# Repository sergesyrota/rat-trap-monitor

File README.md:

Power consumption with deep sleep mode (ping every 5 min): ~70mW?

Power consumption without deep sleep: ~700mW?

Calibration values for voltage conversion
```
1066 -> 10.5V
1142 -> 11.3V
1211 -> 11.9V
1274 -> 12.6V
1407 -> 13.9V
```

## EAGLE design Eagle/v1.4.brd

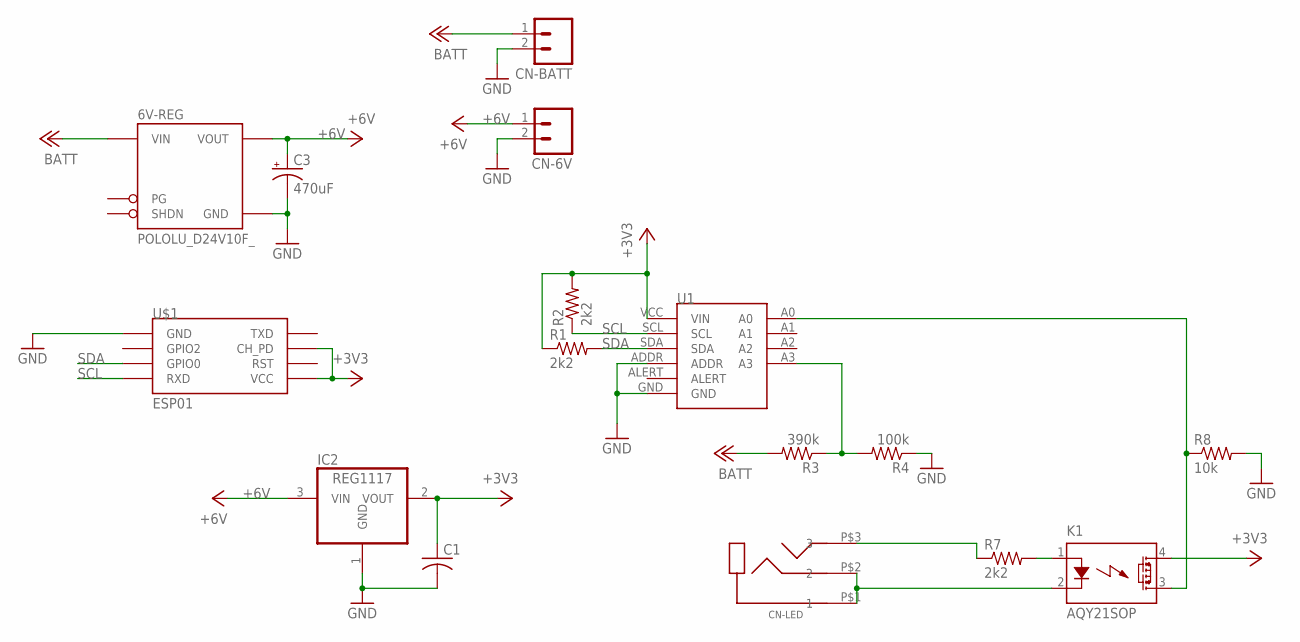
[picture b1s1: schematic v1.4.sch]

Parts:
6V-REG: POLOLU_D24V10F_; POLOLU_D24V10
C1: C-USC1210; C1210
C3: 470uF; CPOL-RADIAL-2.5MM-6.5MM
CN-6V: M02; 02P
CN-BATT: M02; 02P
CN-LED: PJ-320B
IC2: REG1117; SOT223
K1: AQY21SOP; SOP04
R1, R2, R7: 2k2; R0603
R3: 390k; R0603
R4: 100k; R0603
R8: 10k; R0603
U1: GY-ADS1115THM; GY-ADS1115-THM
U$1: ESP01

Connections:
+3V3: C1.1, IC2.2 (VOUT), K1.4 (DS1), R1.1, R2.2, U1.VCC (VIN), U$1.CH_PD, U$1.VCC
+6V: 6V-REG.VOUT, C3.1 (+), CN-6V.1, IC2.3 (VIN)
+12V: 6V-REG.VIN, CN-BATT.1, R3.2
GND: 6V-REG.GND, C1.2, C3.2 (-), CN-6V.2, CN-BATT.2, IC2.1 (GND), R4.1, R8.2, U1.ADDR, U1.GND, U$1.GND
unnamed: K1.1 (A), R7.2
unnamed: R3.1, R4.2, U1.A3
unnamed: CN-LED.P$3 (3), R7.1
unnamed: K1.3 (DS2), R8.1, U1.A0
unnamed: CN-LED.P$1 (1), CN-LED.P$2 (2), K1.2 (K)
SCL: R2.1, U1.SCL, U$1.RX (RXD)
SDA: R1.2, U1.SDA, U$1.GPIO0

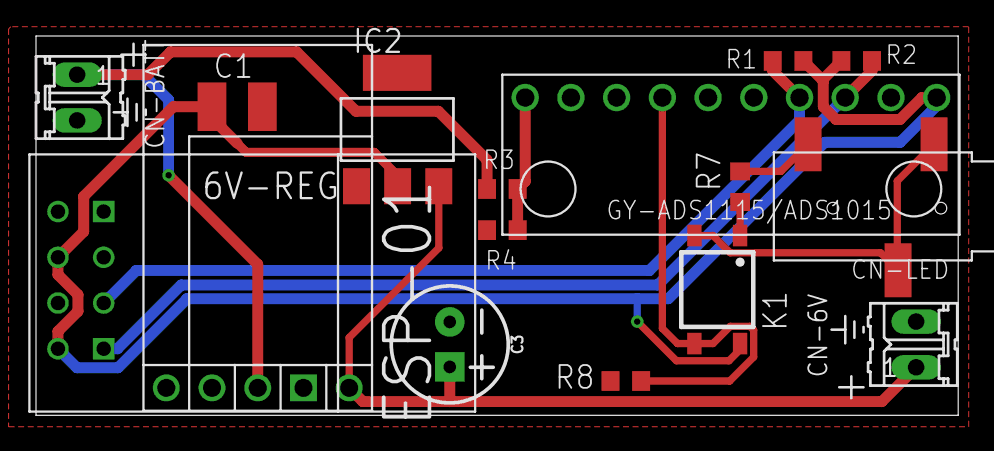
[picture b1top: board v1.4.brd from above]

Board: 2 copper layers, 51.2 x 21.1 mm, 16 parts (0 on the bottom side), 11 nets.

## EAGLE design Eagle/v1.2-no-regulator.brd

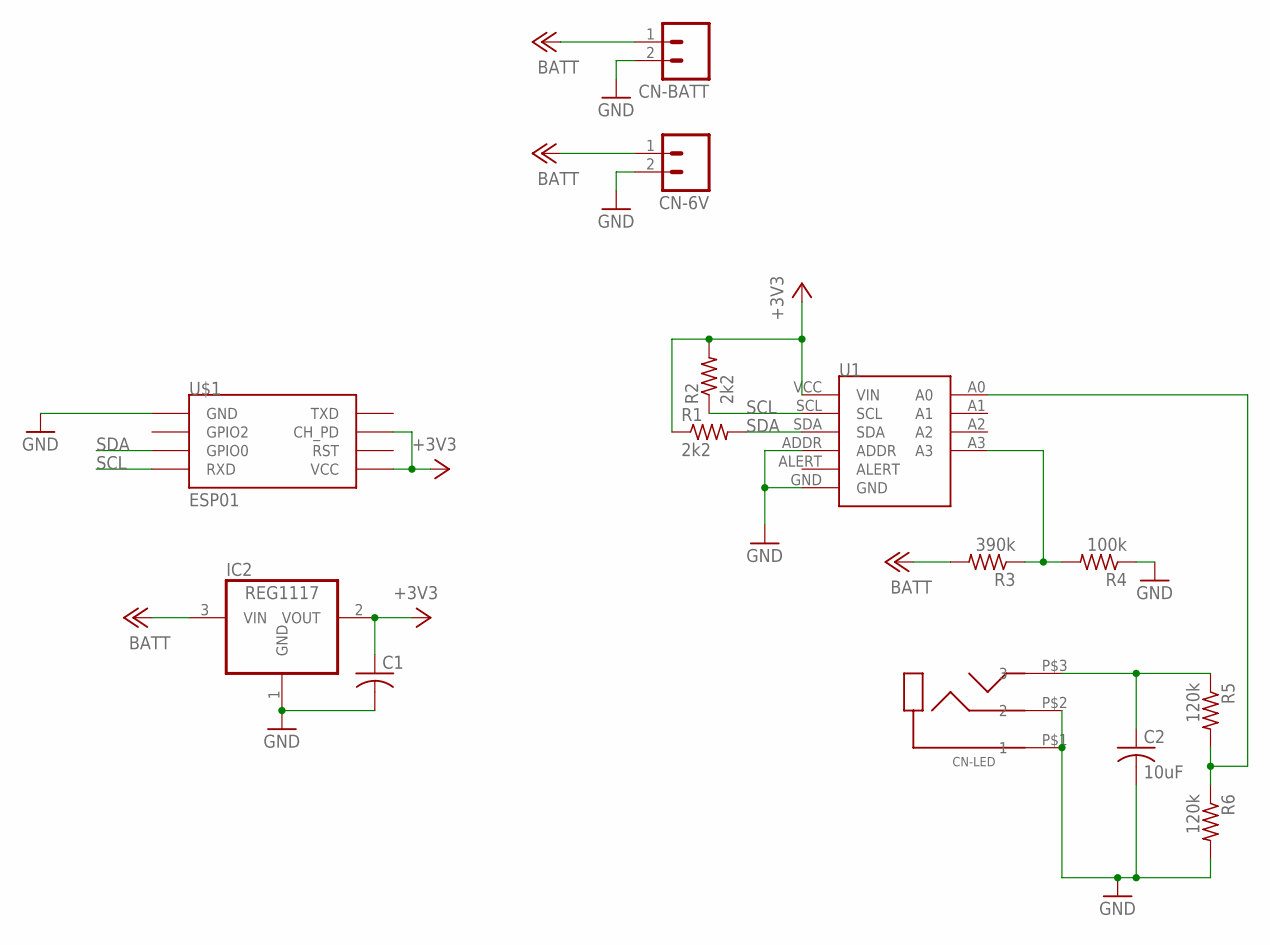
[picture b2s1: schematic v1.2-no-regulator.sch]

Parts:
C1: C-USC1210; C1210
C2: 10uF; C0805K
CN-6V: M02; 02P
CN-BATT: M02; 02P
CN-LED: PJ-320B
IC2: REG1117; SOT223
R1, R2: 2k2; R0603
R3: 390k; R0603
R4: 100k; R0603
R5, R6: 120k; R0603
U1: GY-ADS1115THM; GY-ADS1115-THM
U$1: ESP01

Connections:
+3V3: C1.1, IC2.2 (VOUT), R1.1, R2.2, U1.VCC (VIN), U$1.CH_PD, U$1.VCC
+6V: CN-6V.1, CN-BATT.1, IC2.3 (VIN), R3.2
GND: C1.2, C2.2, CN-6V.2, CN-BATT.2, CN-LED.P$1 (1), CN-LED.P$2 (2), IC2.1 (GND), R4.1, R6.2, U1.ADDR, U1.GND, U$1.GND
unnamed: R3.1, R4.2, U1.A3
unnamed: R5.2, R6.1, U1.A0
unnamed: C2.1, CN-LED.P$3 (3), R5.1
SCL: R2.1, U1.SCL, U$1.RX (RXD)
SDA: R1.2, U1.SDA, U$1.GPIO0

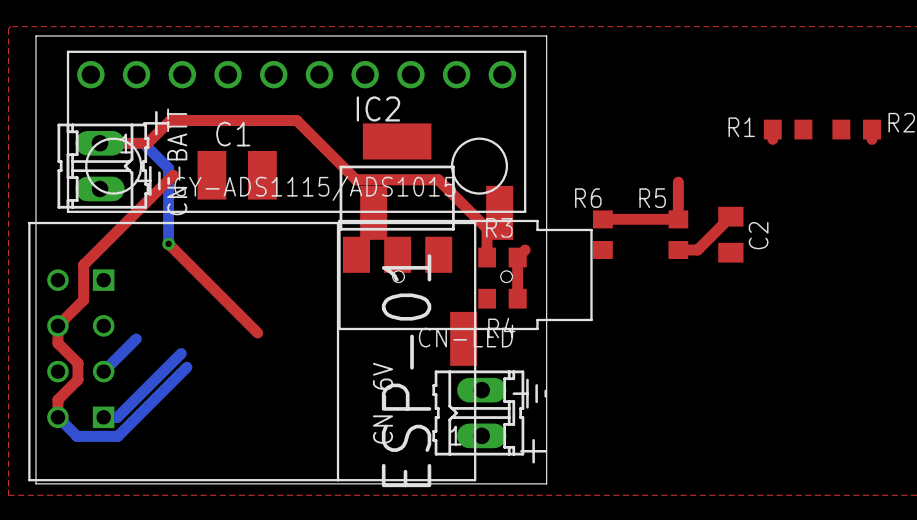
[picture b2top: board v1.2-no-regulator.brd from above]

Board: 2 copper layers, 28.4 x 24.9 mm, 14 parts (0 on the bottom side), 8 nets.

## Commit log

2024-01-01 Adding working version that was developed over some time...
2024-01-02 Adding stats storage to permanent memory

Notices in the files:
parts and their libraries:
SparkFun-Capacitors: Licensing: Creative Commons ShareAlike 4.0 International - https://creativecommons.org/licenses/by-sa/4.0
